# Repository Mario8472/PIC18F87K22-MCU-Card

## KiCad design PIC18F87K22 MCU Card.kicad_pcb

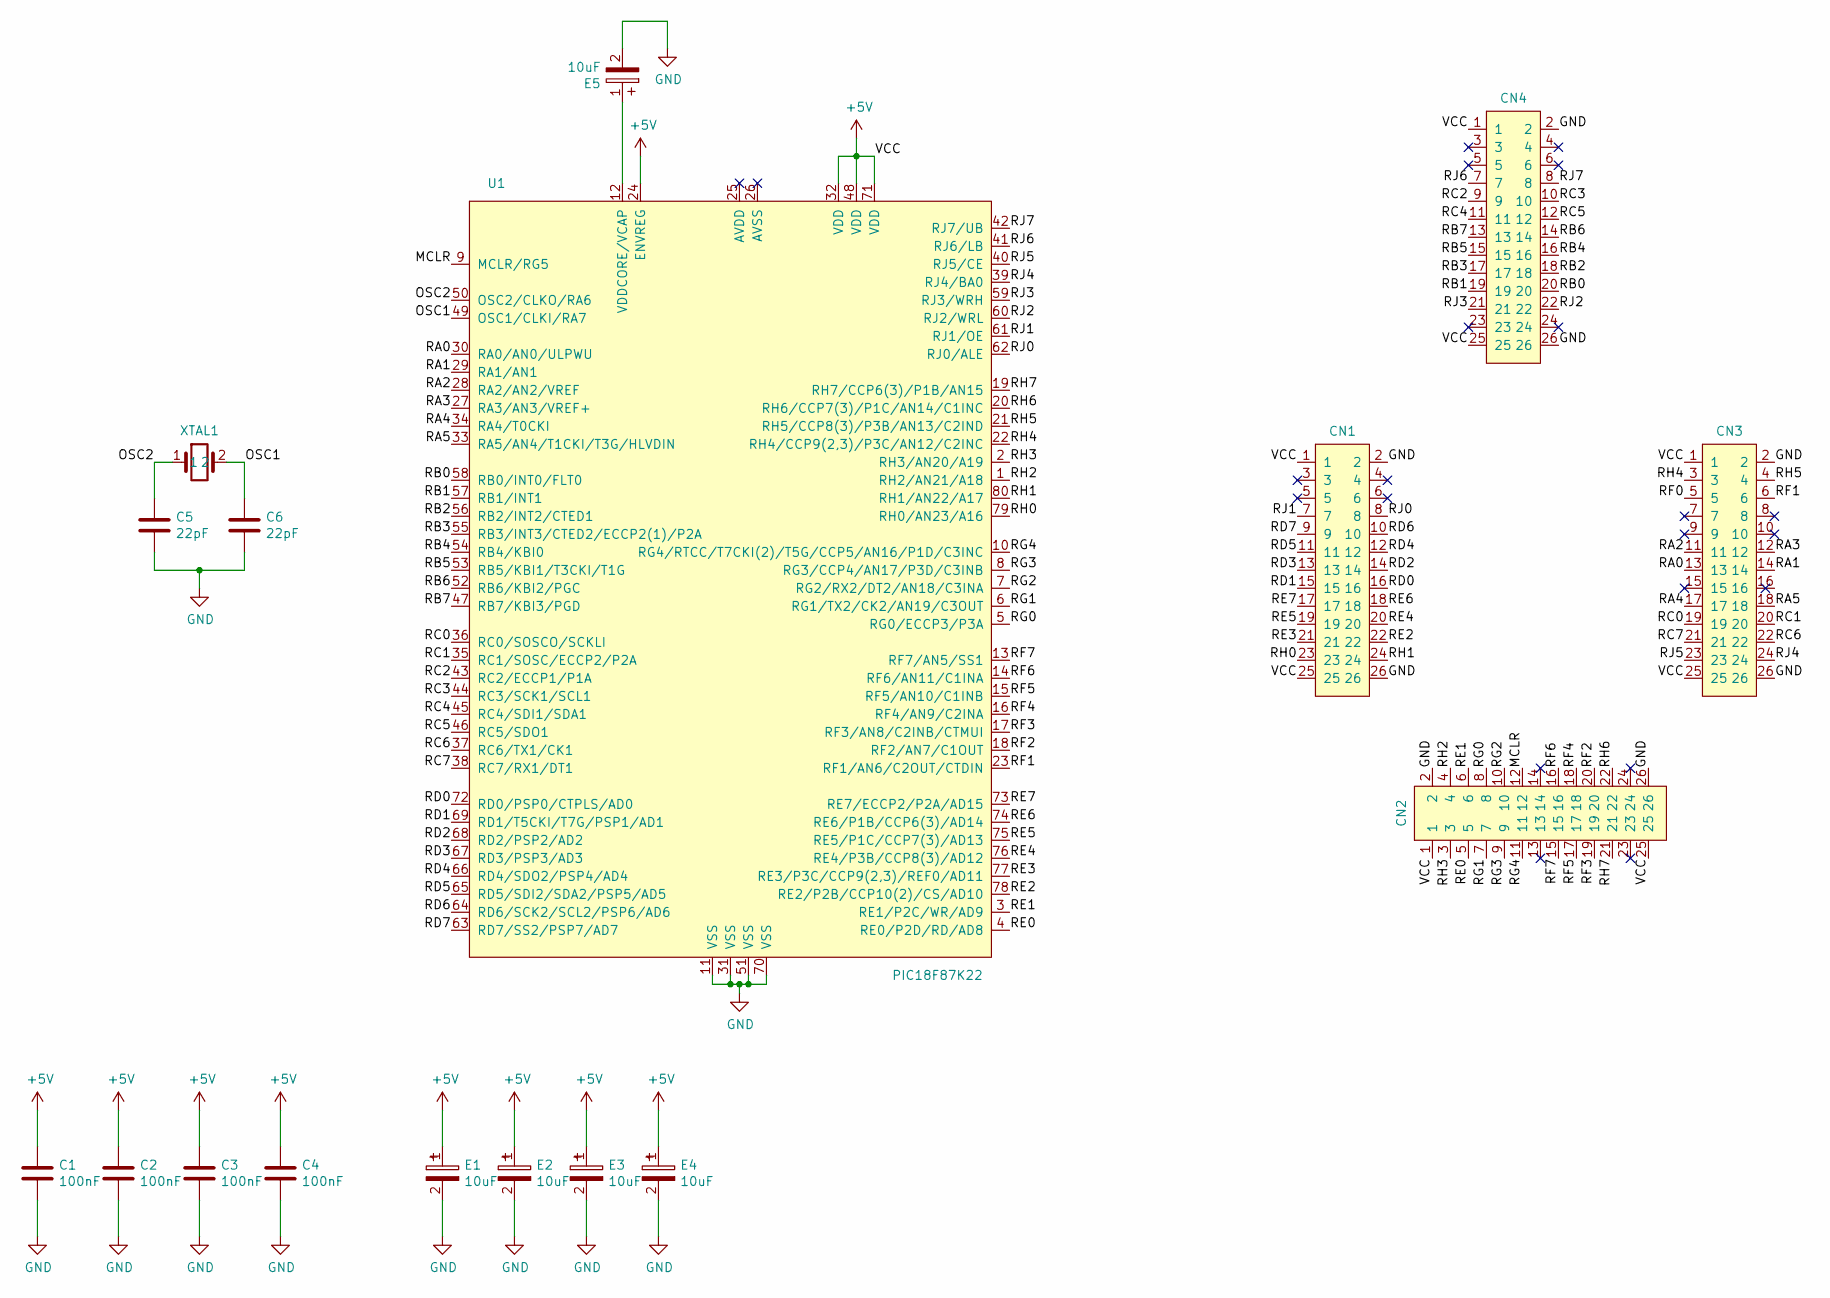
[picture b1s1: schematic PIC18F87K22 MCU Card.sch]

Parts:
C1, C2, C3, C4: 100nF; C_0805_2012Metric
C5, C6: 22pF; C_0805_2012Metric
CN1, CN2, CN3, CN4: PinSocket_2x13_2.54mm; SocketPin_2x13_2.54mm
E1, E2, E3, E4, E5: 10uF; CAP_TANTALUM
U1: PIC18F87K22
XTAL1: QuartzCrystal_SMD; QuartzCrystal_HC49

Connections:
+5V: C1.1, C2.1, C3.1, C4.1, CN1.1, CN1.25, CN2.1, CN2.25, CN3.1, CN3.25, CN4.1, CN4.25, E1.1, E2.1, E3.1, E4.1, U1.24 (ENVREG), U1.32 (VDD), U1.48 (VDD), U1.71 (VDD)
/MCLR: CN2.12, U1.9 (MCLR/RG5)
/OSC1: C6.1, U1.49 (OSC1/CLKI/RA7), XTAL1.2
/OSC2: C5.1, U1.50 (OSC2/CLKO/RA6), XTAL1.1
/RA0: CN3.13, U1.30 (RA0/AN0/ULPWU)
/RA1: CN3.14, U1.29 (RA1/AN1)
/RA2: CN3.11, U1.28 (RA2/AN2/VREF)
/RA3: CN3.12, U1.27 (RA3/AN3/VREF+)
/RA4: CN3.17, U1.34 (RA4/T0CKI)
/RA5: CN3.18, U1.33 (RA5/AN4/T1CKI/T3G/HLVDIN)
/RB0: CN4.20, U1.58 (RB0/INT0/FLT0)
/RB1: CN4.19, U1.57 (RB1/INT1)
/RB2: CN4.18, U1.56 (RB2/INT2/CTED1)
/RB3: CN4.17, U1.55 (RB3/INT3/CTED2/ECCP2(1)/P2A)
/RB4: CN4.16, U1.54 (RB4/KBI0)
/RB5: CN4.15, U1.53 (RB5/KBI1/T3CKI/T1G)
/RB6: CN4.14, U1.52 (RB6/KBI2/PGC)
/RB7: CN4.13, U1.47 (RB7/KBI3/PGD)
/RC0: CN3.19, U1.36 (RC0/SOSCO/SCKLI)
/RC1: CN3.20, U1.35 (RC1/SOSC/ECCP2/P2A)
/RC2: CN4.9, U1.43 (RC2/ECCP1/P1A)
/RC3: CN4.10, U1.44 (RC3/SCK1/SCL1)
/RC4: CN4.11, U1.45 (RC4/SDI1/SDA1)
/RC5: CN4.12, U1.46 (RC5/SDO1)
/RC6: CN3.22, U1.37 (RC6/TX1/CK1)
/RC7: CN3.21, U1.38 (RC7/RX1/DT1)
/RD0: CN1.16, U1.72 (RD0/PSP0/CTPLS/AD0)
/RD1: CN1.15, U1.69 (RD1/T5CKI/T7G/PSP1/AD1)
/RD2: CN1.14, U1.68 (RD2/PSP2/AD2)
/RD3: CN1.13, U1.67 (RD3/PSP3/AD3)
/RD4: CN1.12, U1.66 (RD4/SDO2/PSP4/AD4)
/RD5: CN1.11, U1.65 (RD5/SDI2/SDA2/PSP5/AD5)
/RD6: CN1.10, U1.64 (RD6/SCK2/SCL2/PSP6/AD6)
/RD7: CN1.9, U1.63 (RD7/SS2/PSP7/AD7)
/RE0: CN2.5, U1.4 (RE0/P2D/RD/AD8)
/RE1: CN2.6, U1.3 (RE1/P2C/WR/AD9)
/RE2: CN1.22, U1.78 (RE2/P2B/CCP10(2)/CS/AD10)
/RE3: CN1.21, U1.77 (RE3/P3C/CCP9(2,3)/REF0/AD11)
/RE4: CN1.20, U1.76 (RE4/P3B/CCP8(3)/AD12)
/RE5: CN1.19, U1.75 (RE5/P1C/CCP7(3)/AD13)
/RE6: CN1.18, U1.74 (RE6/P1B/CCP6(3)/AD14)
/RE7: CN1.17, U1.73 (RE7/ECCP2/P2A/AD15)
/RF0: CN3.5
/RF1: CN3.6, U1.23 (RF1/AN6/C2OUT/CTDIN)
/RF2: CN2.20, U1.18 (RF2/AN7/C1OUT)
/RF3: CN2.19, U1.17 (RF3/AN8/C2INB/CTMUI)
/RF4: CN2.18, U1.16 (RF4/AN9/C2INA)
/RF5: CN2.17, U1.15 (RF5/AN10/C1INB)
/RF6: CN2.16, U1.14 (RF6/AN11/C1INA)
/RF7: CN2.15, U1.13 (RF7/AN5/SS1)
/RG0: CN2.8, U1.5 (RG0/ECCP3/P3A)
/RG1: CN2.7, U1.6 (RG1/TX2/CK2/AN19/C3OUT)
/RG2: CN2.10, U1.7 (RG2/RX2/DT2/AN18/C3INA)
/RG3: CN2.9, U1.8 (RG3/CCP4/AN17/P3D/C3INB)
/RG4: CN2.11, U1.10 (RG4/RTCC/T7CKI(2)/T5G/CCP5/AN16/P1D/C3I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)
/RH0: CN1.23, U1.79 (RH0/AN23/A16)
/RH1: CN1.24, U1.80 (RH1/AN22/A17)
/RH2: CN2.4, U1.1 (RH2/AN21/A18)
/RH3: CN2.3, U1.2 (RH3/AN20/A19)
/RH4: CN3.3, U1.22 (RH4/CCP9(2,3)/P3C/AN12/C2INC)
/RH5: CN3.4, U1.21 (RH5/CCP8(3)/P3B/AN13/C2IND)
/RH6: CN2.22, U1.20 (RH6/CCP7(3)/P1C/AN14/C1INC)
/RH7: CN2.21, U1.19 (RH7/CCP6(3)/P1B/AN15)
/RJ0: CN1.8, U1.62 (RJ0/ALE)
/RJ1: CN1.7, U1.61 (RJ1/OE)
/RJ2: CN4.22, U1.60 (RJ2/WRL)
/RJ3: CN4.21, U1.59 (RJ3/WRH)
/RJ4: CN3.24, U1.39 (RJ4/BA0)
/RJ5: CN3.23, U1.40 (RJ5/CE)
/RJ6: CN4.7, U1.41 (RJ6/LB)
/RJ7: CN4.8, U1.42 (RJ7/UB)
GND: C1.2, C2.2, C3.2, C4.2, C5.2, C6.2, CN1.2, CN1.26, CN2.2, CN2.26, CN3.2, CN3.26, CN4.2, CN4.26, E1.2, E2.2, E3.2, E4.2, E5.2, U1.11 (VSS), U1.31 (VSS), U1.51 (VSS), U1.70 (VSS)
unnamed: E5.1, U1.12 (VDDCORE/VCAP)

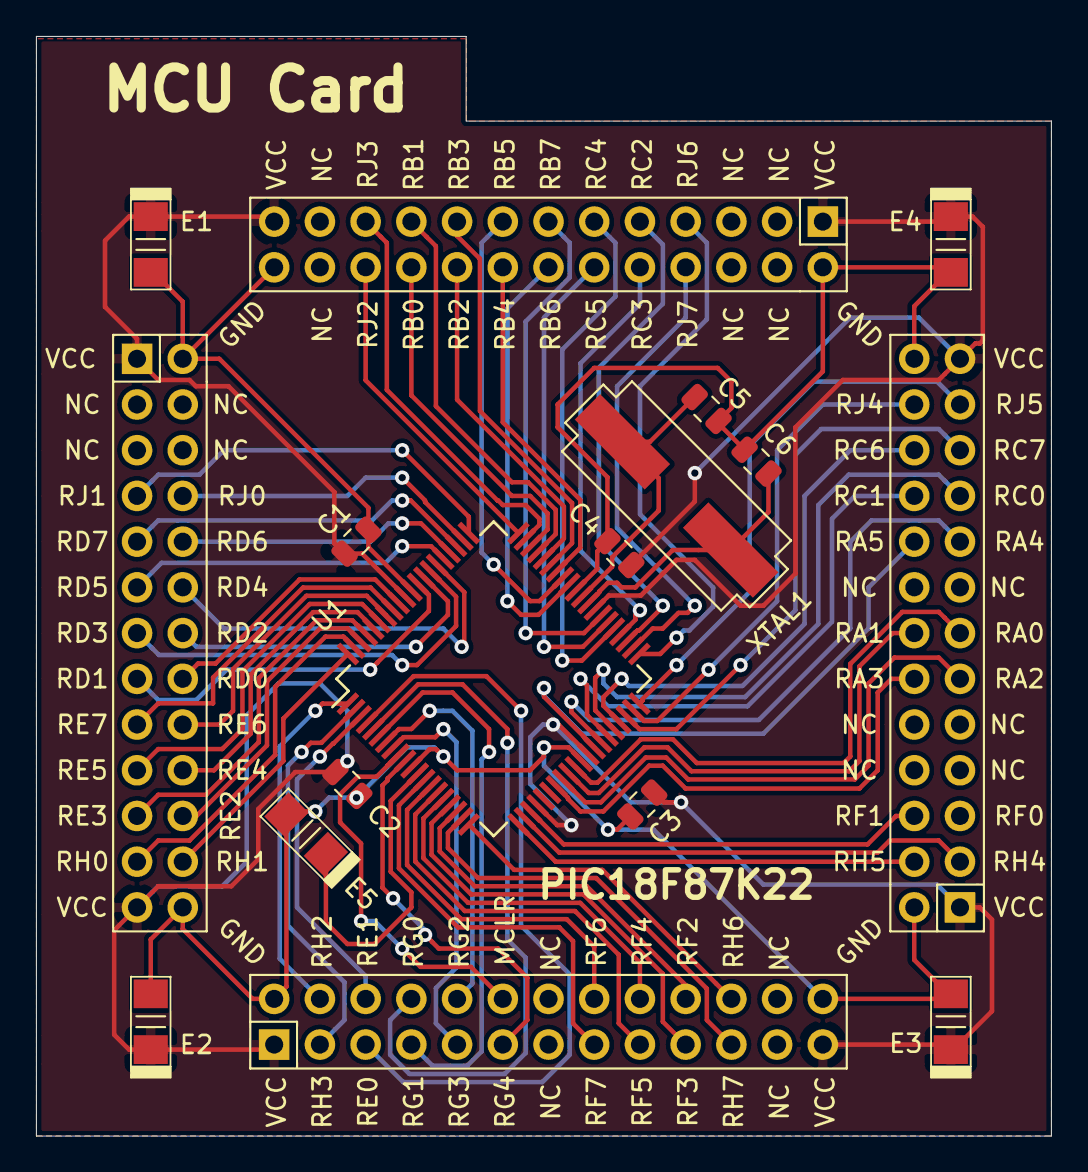
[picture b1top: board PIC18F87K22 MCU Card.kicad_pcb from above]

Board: 2 copper layers, 56.4 x 61.1 mm, 17 parts (0 on the bottom side), 72 nets.
